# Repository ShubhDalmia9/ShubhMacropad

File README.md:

OVERVIEW :
-
A compact 9-key macropad with a rotary encoder, built using a custom PCB and QMK firmware. It features three modes—Study, Creative, and Focus—each mapped to practical shortcuts for productivity, media control, and navigation, enabling efficient workflow switching.

How to use :
-
- Plug the macropad into your computer or a power source
- Select a mode using the top row keys  
- Use the remaining keys for the shortcuts
- Rotate the encoder to control volume level

 Why I made this :
 -
 - The functions of this macropad can help me in my daily life.
 - To reduce repetitive keyboard shortcuts
 - To reduce repetitive keyboard shortcuts

FEATURES :
-
- EC11 Rotary encoder for controlling volume
- 9 Keys

CAD DESIGN :
-
- The case uses 2 parts the bottom and upper half
- The 2 parts can be joined by using 4 M3 screws
- The PCB sits on the bottom half and is coverd by the upperhalf

fully assembled

Part Stuidio

 - The Design was made in OnShape
 - Design Link :
   https://cad.onshape.com/documents/a280f0894019be8d3362bd64/w/67d5e1344d4c93c18eda979f/e/d96660c4f28b5cc322d90e8b?renderMode=0&uiState=69c8c5cffc6171d5b9f8606e

PCB :
-
- The PCB was made in KiCad

Schematic

PCB

3D View OF PCB

FIRMWARE OVERVIEW :
-
This macropad uses QMK firmware for everything.

The 9 keys are split into 3 modes: Study, Creative, and Focus.
The top row is used to switch between modes.

Each mode changes what the remaining 6 keys do:
- Study mode is for basic shortcuts like copy, paste, undo, redo, and save
- Creative mode is for zoom, media control, brightness, and mute
- Focus mode is for volume control and simple navigation

The rotary encoder is used for volume control.

BOM :
-
EVERYTHING required to make this Hackpad:

- 1x XIAO RP2040
- 9x Cherry MX Switches
- 9x DSA Keycaps
- 4x M3x16mm SHCS Bolts
- 9x 1N4148 DO-35 Diodes.
- 1x Case (2 printed parts)
- 1x EC11 Rotary Encoder with switch

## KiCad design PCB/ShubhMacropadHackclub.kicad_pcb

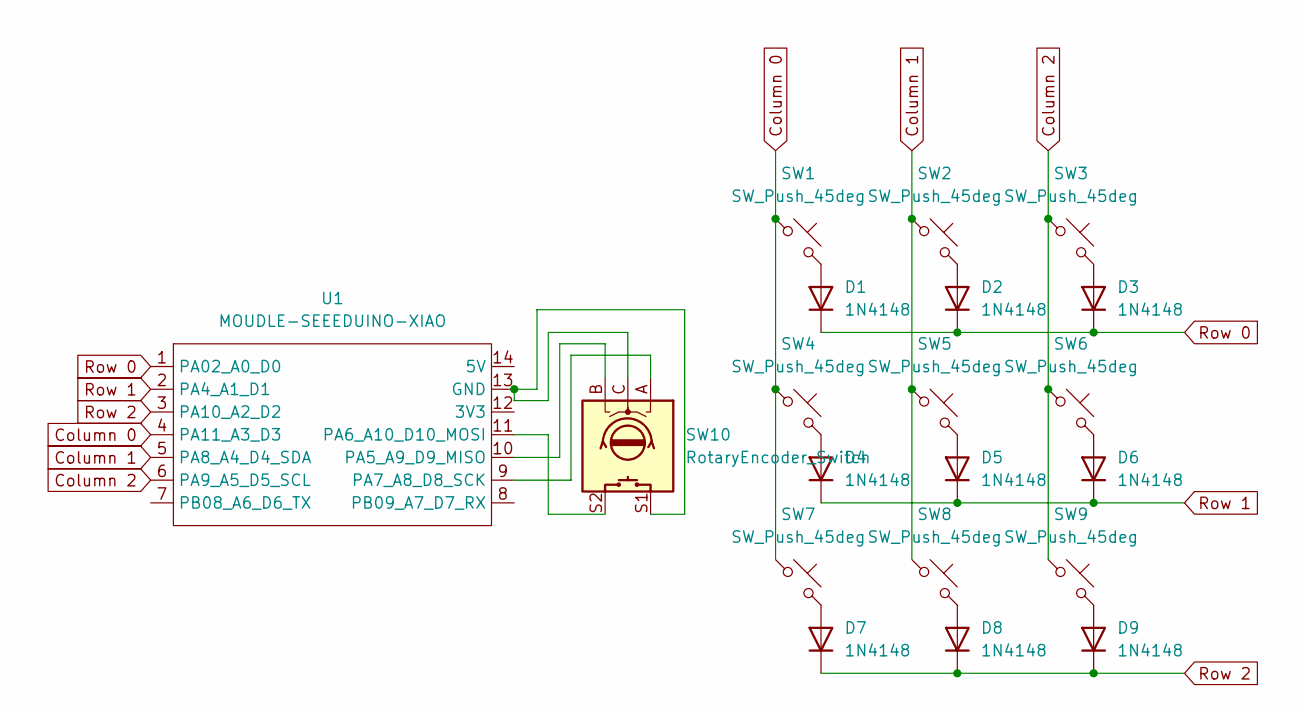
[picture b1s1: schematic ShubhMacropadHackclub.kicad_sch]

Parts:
D1, D2, D3, D4, D5, D6, D7, D8, D9: 1N4148; D_DO-35_SOD27_P7.62mm_Horizontal
SW1, SW2, SW3, SW4, SW5, SW6, SW7, SW8, SW9: SW_Push_45deg; SW_Cherry_MX_1.00u_PCB
SW10: RotaryEncoder_Switch; RotaryEncoder_Alps_EC11E-Switch_Vertical_H20mm_CircularMoun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
U1: MOUDLE-SEEEDUINO-XIAO; XIAO-Generic-Hybrid-14P-2.54-21X17.8MM

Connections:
Column 0: SW1.1, SW4.1, SW7.1, U1.4 (PA11_A3_D3)
Column 1: SW2.1, SW5.1, SW8.1, U1.5 (PA8_A4_D4_SDA)
Column 2: SW3.1, SW6.1, SW9.1, U1.6 (PA9_A5_D5_SCL)
unnamed: D1.2 (A), SW1.2
unnamed: D2.2 (A), SW2.2
unnamed: D3.2 (A), SW3.2
unnamed: D4.2 (A), SW4.2
unnamed: D5.2 (A), SW5.2
unnamed: D6.2 (A), SW6.2
unnamed: D7.2 (A), SW7.2
unnamed: D8.2 (A), SW8.2
unnamed: D9.2 (A), SW9.2
unnamed: SW10.C, SW10.S1, U1.13 (GND)
unnamed: SW10.B, U1.10 (PA5_A9_D9_MISO)
unnamed: SW10.S2, U1.11 (PA6_A10_D10_MOSI)
unnamed: SW10.A, U1.9 (PA7_A8_D8_SCK)
Row 0: D1.1 (K), D2.1 (K), D3.1 (K), U1.1 (PA02_A0_D0)
Row 1: D4.1 (K), D5.1 (K), D6.1 (K), U1.2 (PA4_A1_D1)
Row 2: D7.1 (K), D8.1 (K), D9.1 (K), U1.3 (PA10_A2_D2)

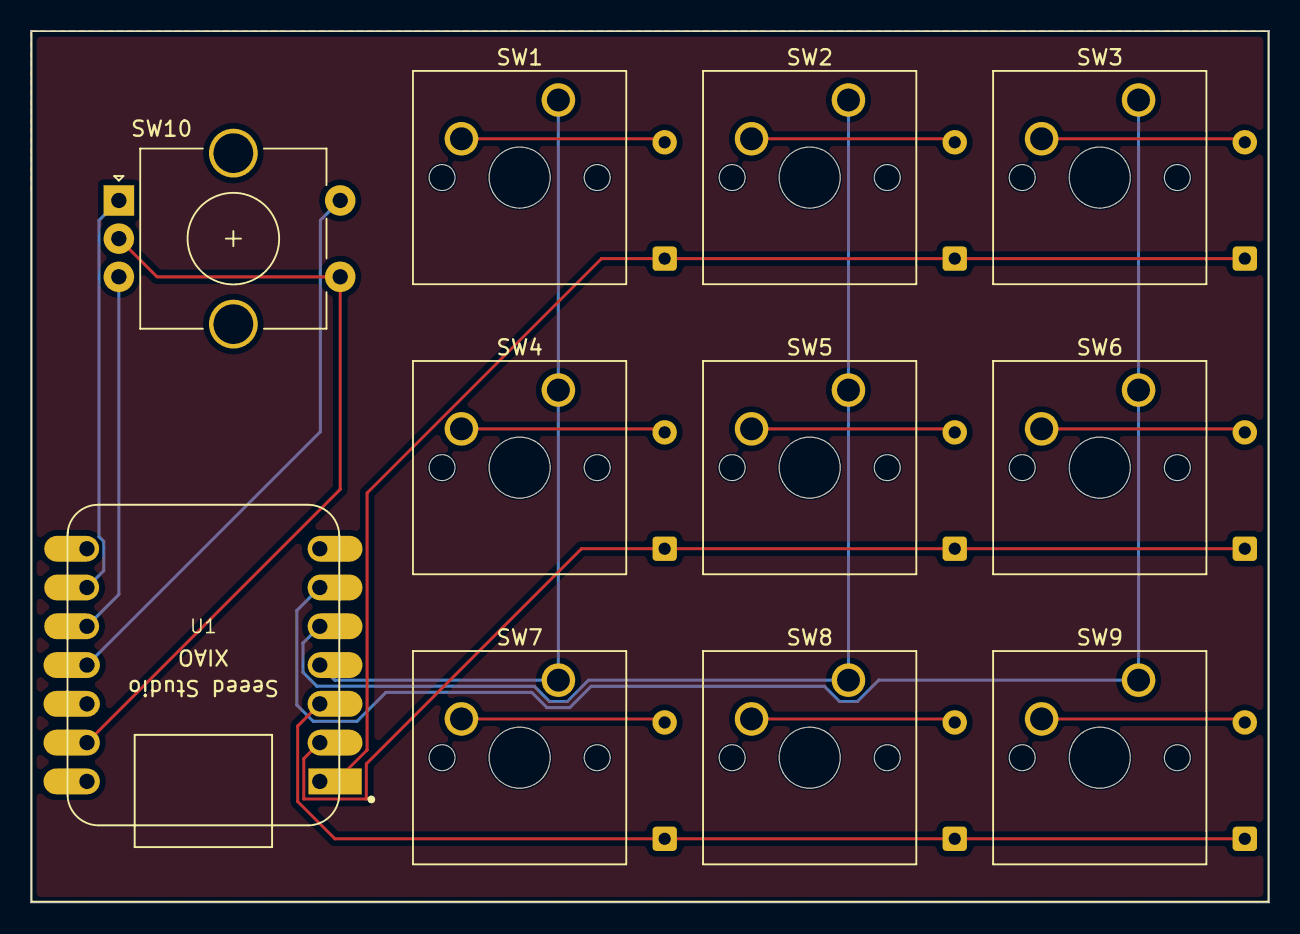
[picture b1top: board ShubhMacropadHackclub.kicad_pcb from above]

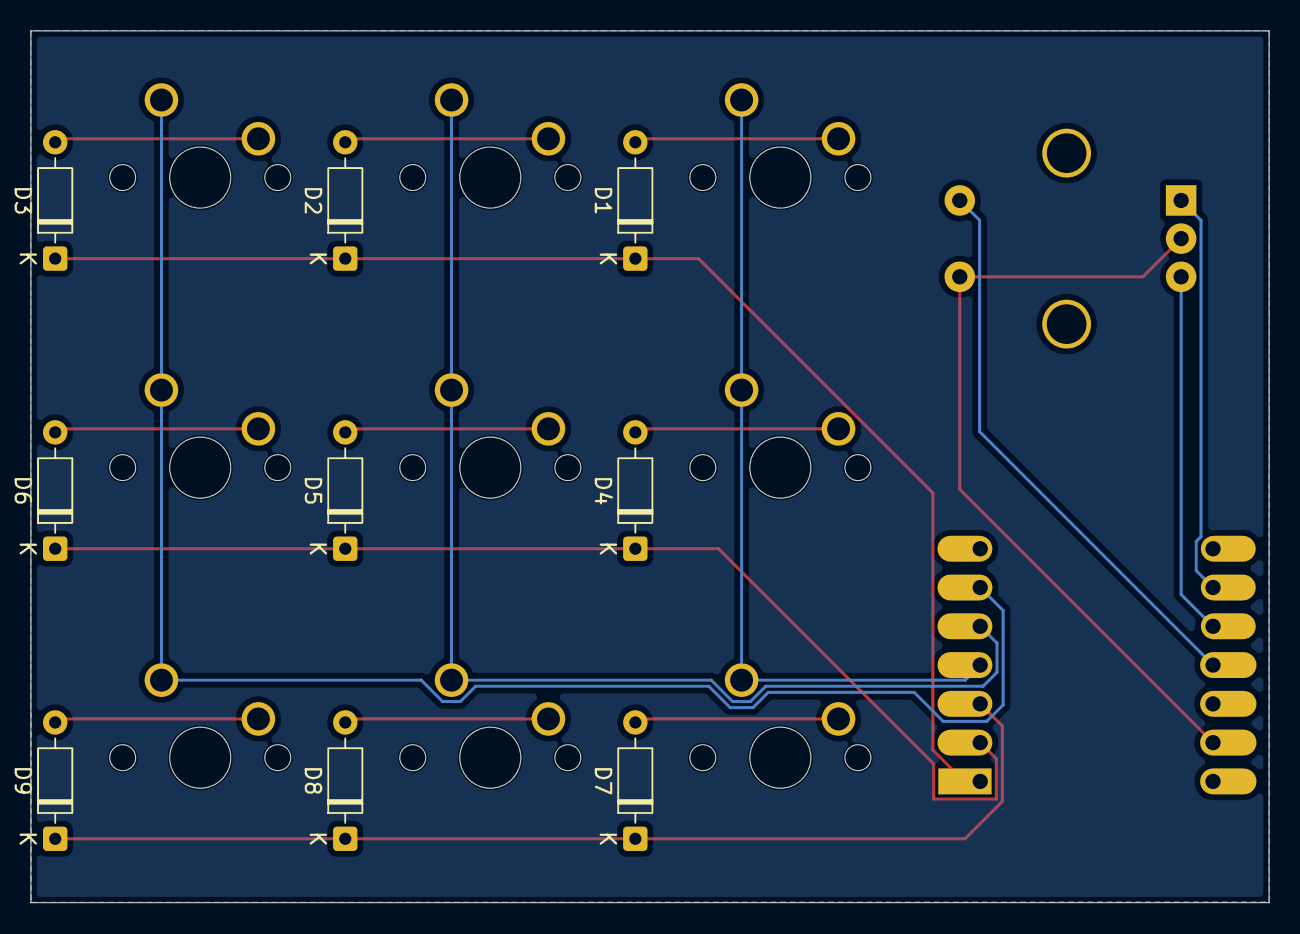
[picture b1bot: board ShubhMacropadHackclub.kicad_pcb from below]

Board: 2 copper layers, 81.1 x 57.1 mm, 20 parts (9 on the bottom side), 19 nets.

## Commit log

2026-03-29 README.md
2026-03-29 Create CAD
2026-03-29 Create pic
2026-03-29 Create keymap
